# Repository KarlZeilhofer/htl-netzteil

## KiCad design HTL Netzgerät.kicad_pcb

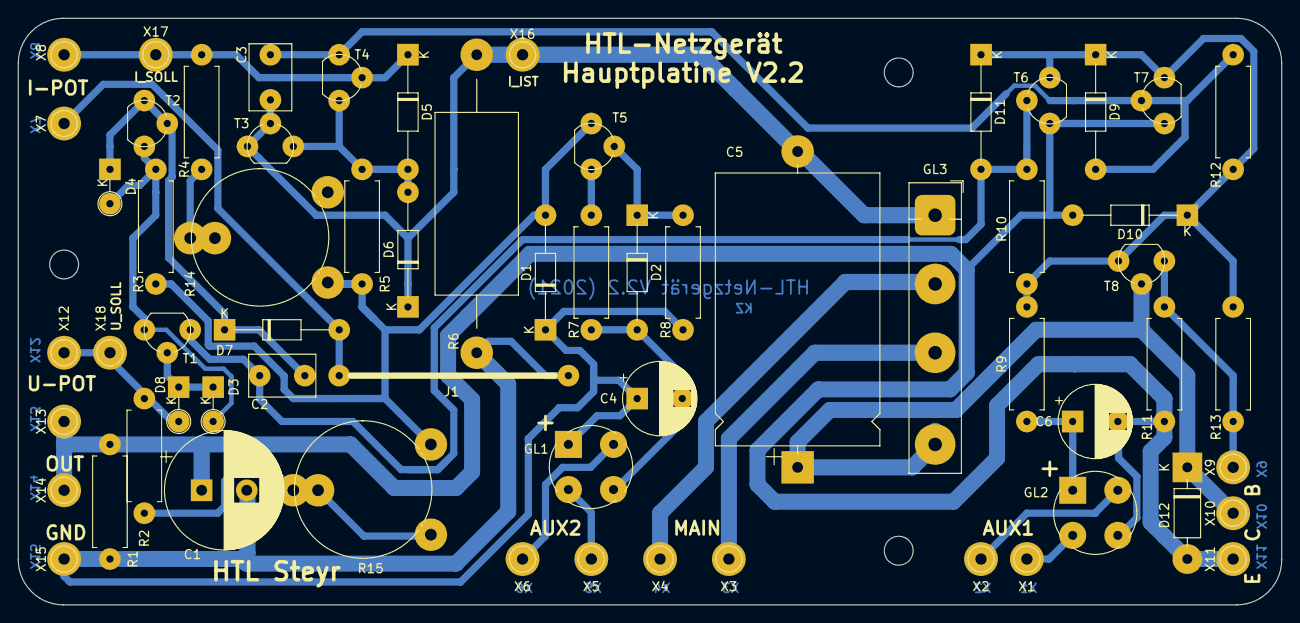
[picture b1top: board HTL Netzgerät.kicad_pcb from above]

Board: 2 copper layers, 140.0 x 65.0 mm, 66 parts (0 on the bottom side), 28 nets.

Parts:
C1: 470u; CP_Radial_D13.0mm_P5.00mm
C2, C3: 3n3; C_Rect_L7.2mm_W4.5mm_P5.00mm_FKS2_FKP2_MKS2_MKP2
C4: 47u; CP_Radial_D8.0mm_P5.00mm
C5: 2200u; CP_Axial_L30.0mm_D18.0mm_P35.00mm_Horizontal
C6: 100u; CP_Radial_D8.0mm_P5.00mm
D1: 33V; D_DO-35_SOD27_P12.70mm_Horizontal
D2: 5V6; D_DO-35_SOD27_P12.70mm_Horizontal
D3, D4, D8: 1N4148; D_DO-35_SOD27_P3.81mm_Vertical_KathodeUp
D5, D6, D7, D9, D10, D11: 1N4148; D_DO-35_SOD27_P12.70mm_Horizontal
D12: 1N4007; D_DO-41_SOD81_P10.16mm_Horizontal
GL1, GL2: 1A; Diode_Bridge_Round_D9.0mm
GL3: 3A; Brueckengleichrichter_p7.4-7.2-9.5mm
J1: 0.7/25.4mm; Drahtbruecke_d0.7mm_P20.32mm
MK1, MK2, MK3: Mounting_Hole; MountingHole_3.2mm_M3
R1: 2k2; R_Axial_DIN0411_L9.9mm_D3.6mm_P12.70mm_Horizontal
R2: 47k; R_Axial_DIN0411_L9.9mm_D3.6mm_P12.70mm_Horizontal
R3, R5: 330k; R_Axial_DIN0411_L9.9mm_D3.6mm_P12.70mm_Horizontal
R4: 120k; R_Axial_DIN0411_L9.9mm_D3.6mm_P12.70mm_Horizontal
R6: 0R22/5W; R_Axial_DIN0922_L20.0mm_D9.0mm_P30.48mm_Horizontal
R7: 1k; R_Axial_DIN0411_L9.9mm_D3.6mm_P12.70mm_Horizontal
R8, R11: 10k; R_Axial_DIN0411_L9.9mm_D3.6mm_P12.70mm_Horizontal
R9, R13: 27k; R_Axial_DIN0411_L9.9mm_D3.6mm_P12.70mm_Horizontal
R10, R12: 220k; R_Axial_DIN0411_L9.9mm_D3.6mm_P12.70mm_Horizontal
R14: 25k; Potentiometer_Piher_PT-15-V02_Vertical
R15: 50k; Potentiometer_Piher_PT-15-V02_Vertical
T1, T2, T3, T4, T5: BC547; TO-92
T6, T7: BC557; TO-92
T8: BC639; TO-92
X1: AUX1_AC1; Einpress-Stift_Drill1.25mm
X2: AUX1_AC2; Einpress-Stift_Drill1.25mm
X3: MAIN_AC1; Einpress-Stift_Drill1.25mm
X4: MAIN_AC2; Einpress-Stift_Drill1.25mm
X5: AUX2_AC1; Einpress-Stift_Drill1.25mm
X6: AUX2_AC2; Einpress-Stift_Drill1.25mm
X7, X16, X17, X18: IPOT+; Einpress-Stift_Drill1.25mm
X8: IPOT-; Einpress-Stift_Drill1.25mm
X9: B; Einpress-Stift_Drill1.25mm
X10: C; Einpress-Stift_Drill1.25mm
X11: E; Einpress-Stift_Drill1.25mm
X12: VPOT-; Einpress-Stift_Drill1.25mm
X13: VPOT+; Einpress-Stift_Drill1.25mm
X14: OUT; Einpress-Stift_Drill1.25mm
X15: GND; Einpress-Stift_Drill1.25mm

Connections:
/0V: C1.2, C4.1, D1.1, GL1.1, J1.1, R1.1, R6.2, R8.2, X15.1
/-33V: D1.2, R3.1, R5.1, R14.3, R15.1, T5.1
/A_-0.6V: D5.2, D6.2, R5.2, T3.3, T4.3
/B_-1.2V: D3.2, D4.2, R3.2, T1.3, T2.3
/U_AUX1: C6.1, GL2.1, R9.1
/U_AUX2: C4.2, D2.2, GL1.3, R7.1
/U_Main: C5.1, D12.1, GL3.4, T8.2, X10.1
/U_OUT: C1.1, C6.2, D10.2, D12.2, GL2.3, R1.2, R11.1, T6.1, T7.1, X11.1, X13.1, X14.1
/V_I_FB: D5.1, R4.2, T4.2, X8.1, X17.1
/V_I_Ref: C3.2, C5.2, D6.1, GL3.1, R6.1, T3.1, T3.2, X16.1
/V_U_FB: D8.2, R2.2, X12.1, X18.1
/V_U_Ref: C2.2, D4.1, D7.1, T2.1, T2.2
unnamed: C2.1, D11.2, R10.1, T1.1, T6.2
unnamed: C3.1, D9.2, R12.1, T4.1, T7.2
unnamed: D2.1, R8.1, T5.2
unnamed: D3.1, D8.1, T1.2
unnamed: D7.2, J1.2, X7.1
unnamed: D9.1, D10.1, D11.1, R9.2, R10.2, R12.2, R13.2, T6.3, T7.3, T8.3
unnamed: GL1.2, X5.1
unnamed: GL1.4, X6.1
unnamed: GL2.2, X1.1
unnamed: GL2.4, X2.1
unnamed: GL3.2, X4.1
unnamed: GL3.3, X3.1
unnamed: R7.2, T5.3
unnamed: R11.2, R13.1, T8.1, X9.1
unnamed: R4.1, R14.2
unnamed: R2.1, R15.2, R15.3

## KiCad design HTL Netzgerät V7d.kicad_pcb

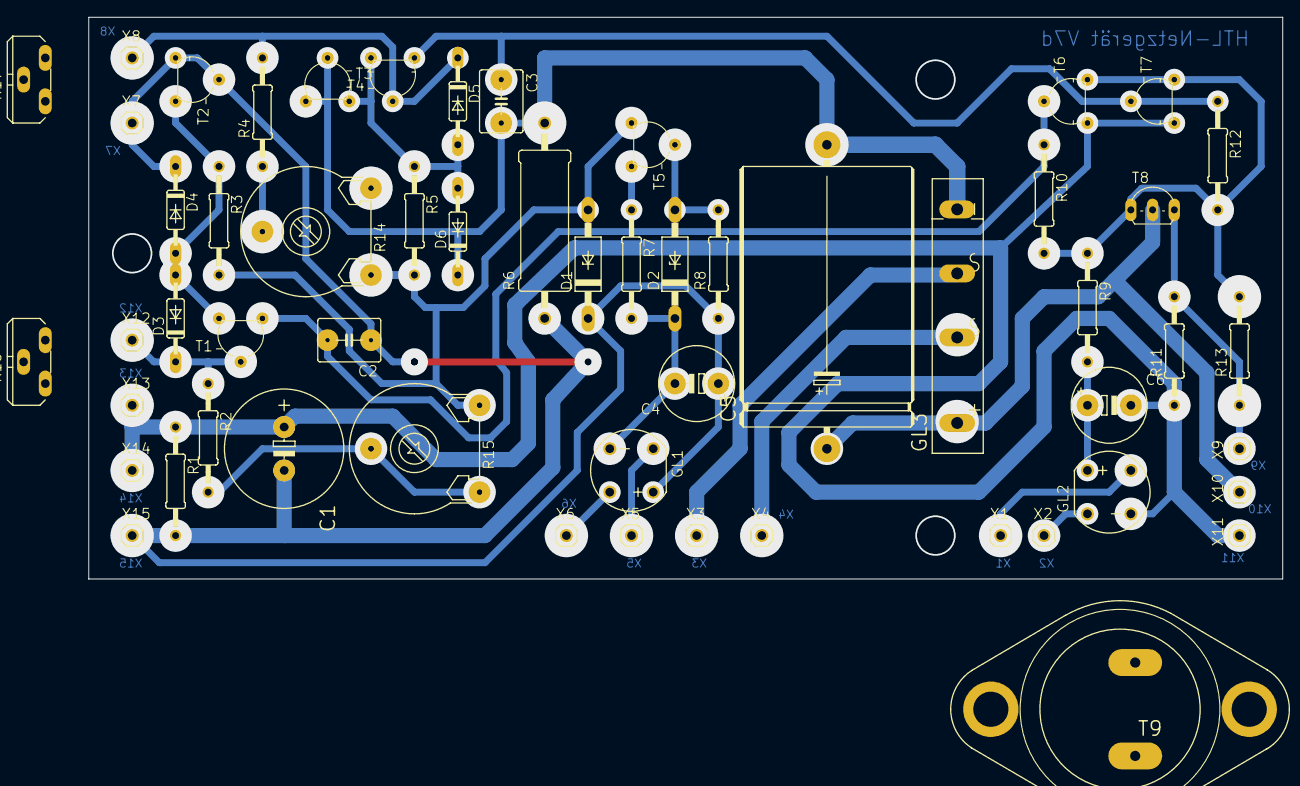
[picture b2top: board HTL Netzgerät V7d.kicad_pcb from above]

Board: 2 copper layers, 139.7 x 65.7 mm, 56 parts (0 on the bottom side), 26 nets.

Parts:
C1: 470u; E5-13
C2, C3: 3,3n; C050-050X075
C4: 47u; E5-8,5
C5: 2200u; E35-18
C6: 100u; E5-8,5
D1, D2: BZY97; F126Z12
D3, D4, D5, D6: 1N4148; DO35-10
GL1, GL2: RB1A
GL3: FB32
R1: 2,2k; 0207_12
R2: 47k; 0207_12
R3, R5: 330k; 0207_12
R4: 120k; 0207_12
R6: 22k; 0617_22
R7: 1k; 0207_12
R8, R11: 10k; 0207_12
R9, R13: 27k; 0207_12
R10, R12: 220k; 0207_12
R14: 25k; LI15
R15: 50k; LI15
R16, R17: TRIM_EU-PT10S; PT-10S
T1, T2, T3, T4, T5: BC547; TO92
T6, T7: BC557; TO92
T8: BC639; TO92-BCE
T9: -NPN-TO3; TO3
X1, X2, X3, X4, X5, X6, X7, X8, X9, X10, X11, X12, X13, X14, X15: PINHD-1X1; 1X01

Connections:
unnamed: C1.+, C6.-, GL2.-, R1.1, R11.1, T6.3, T7.3, X11.1, X13.1, X14.1
unnamed: C1.-, C2.1, D4.C, R1.2, R6.1, T2.2, T2.3, X7.1, X15.1
unnamed: C2.2, R10.1, T1.3, T6.2
unnamed: C3.1, R12.1, T4.3, T7.2
unnamed: C3.2, C5.-, D6.C, GL3.-, R6.2, T3.2, T3.3
unnamed: C4.+, D1.C, GL1.+, R8.1
unnamed: C4.-, D2.C, GL1.-, R7.2
unnamed: C5.+, GL3.+, T8.C, X10.1
unnamed: C6.+, GL2.+, R9.2
unnamed: D1.A, R3.2, R5.2, R14.A, R15.E, T5.3
unnamed: D2.A, R8.2, T5.2
unnamed: D3.A, D4.A, R3.1, T1.1, T2.1
unnamed: D3.C, R2.1, T1.2, X12.1
unnamed: D5.A, D6.A, R5.1, T3.1, T4.1
unnamed: D5.C, R4.2, T4.2, X8.1
unnamed: GL1.AC1, X6.1
unnamed: GL1.AC2, X5.1
unnamed: GL2.AC1, X1.1
unnamed: GL2.AC2, X2.1
unnamed: GL3.AC1, X4.1
unnamed: GL3.AC2, X3.1
unnamed: R7.1, T5.1
unnamed: R9.1, R10.2, R12.2, R13.2, T6.1, T7.1, T8.B
unnamed: R11.2, R13.1, T8.E, X9.1
unnamed: R4.1, R14.S
unnamed: R2.2, R15.A, R15.S

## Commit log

2019-12-21 Version 7d, übernommen von EGLG
2019-12-21 nun mit Reinzeichnung und Kommentaren von mir
2019-12-21 gitignore
2019-12-21 ignore fp-info-cache
2019-12-21 Reinzeichnung ins Hauptdokument verschoben, Hauptdokument gelöscht
2019-12-21 neue footprints zugeordnet im Schaltplan
2019-12-21 Layout soweit fertig, Changelog angepasst, siehe TODOs, eMail an Kollegen
2020-11-16 Libs und TODOs aktualisiert
2020-11-18 Einige Korrekturen eingepflegt für Version 2.1
2020-11-19 Weitere Verbesserungen, Drahtbrücke, Texte, siehe Changelog
2020-11-19 Postcommit
2020-11-19 Fertig zur Produktion, Gerber, Screenshots, Bestückungsdruck, ...
2020-11-20 3D Modell für Trimmer inkl. Screenshot
2021-04-29 v2.2 fertig, 3 Stk. bestellt (einseitig)
    siehe CHANGELOG und Github Issues
